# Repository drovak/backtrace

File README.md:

# backtrace
Automated DEC backplane tracing tool

Double-height Flip-Chip card implementing a set of shift registers to scan the card edge 
connectors for continuity.

Driver card for driving a large number of Flip-Chip cards.

This project is still incomplete and untested, but prototype hardware has been ordered.

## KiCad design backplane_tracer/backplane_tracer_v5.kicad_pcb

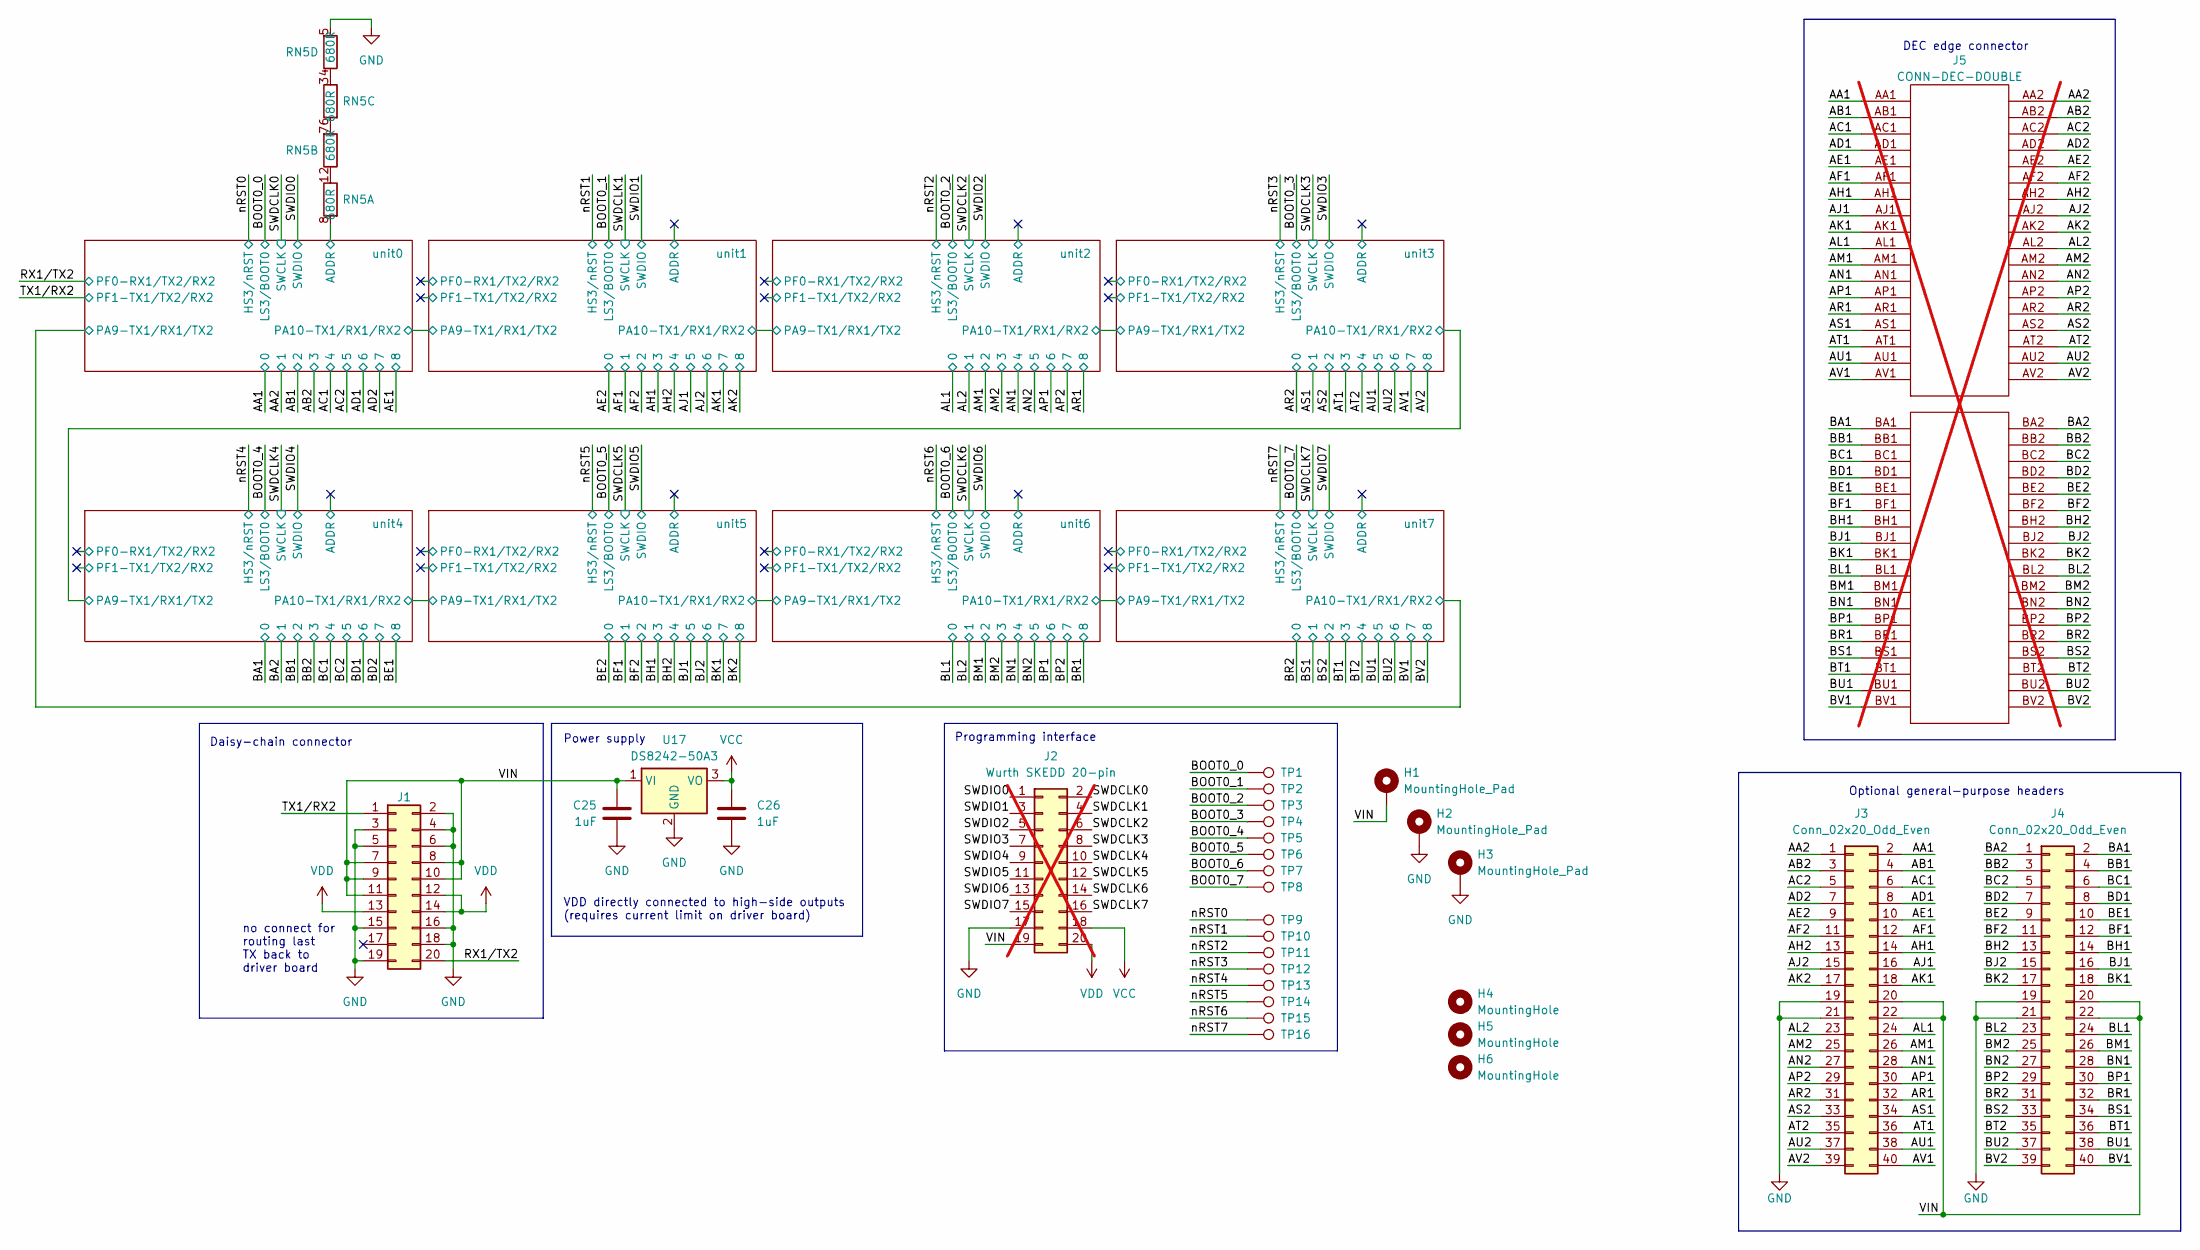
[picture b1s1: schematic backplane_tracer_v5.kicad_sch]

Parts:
C25, C26: 1uF; C_0603_1608Metric; LCSC C15849
H1, H2, H3: MountingHole_Pad; MountingHole_3.7mm_Pad_Via
H4, H5, H6: MountingHole; JLCPCB_Tooling_Hole
J1: 2x10 right angle IDC connector, 2.54mm pitch; IDC-Header_2x10_P2.54mm_Horizontal; LCSC C5372876
J2: Wurth SKEDD 20-pin; wurth_skedd_490107672012; not fitted
J3, J4: Conn_02x20_Odd_Even; PinHeader_2x20_P2.54mm_Vertical; LCSC C5224014
J5: CONN-DEC-DOUBLE; not fitted
RN5: 680R; R_Array_Convex_4x0603; LCSC C12035
TP1, TP2, TP3, TP4, TP5, TP6, TP7, TP8, TP9, TP10, TP11, TP12, TP13, TP14, TP15, TP16: TestPoint; TestPoint_Pad_D1.0mm
U17: DS8242-50A3; SOT-89-3; LCSC C5884136

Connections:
/AA1: J3.2, J5.AA1; also elsewhere on the board
/AA2: J3.1, J5.AA2; also elsewhere on the board
/AB1: J3.4, J5.AB1; also elsewhere on the board
/AB2: J3.3, J5.AB2; also elsewhere on the board
/AC1: J3.6, J5.AC1; also elsewhere on the board
/AC2: J3.5, J5.AC2; also elsewhere on the board
/AD1: J3.8, J5.AD1; also elsewhere on the board
/AD2: J3.7, J5.AD2; also elsewhere on the board
/AE1: J3.10, J5.AE1; also elsewhere on the board
/AE2: J3.9, J5.AE2; also elsewhere on the board
/AF1: J3.12, J5.AF1; also elsewhere on the board
/AF2: J3.11, J5.AF2; also elsewhere on the board
/AH1: J3.14, J5.AH1; also elsewhere on the board
/AH2: J3.13, J5.AH2; also elsewhere on the board
/AJ1: J3.16, J5.AJ1; also elsewhere on the board
/AJ2: J3.15, J5.AJ2; also elsewhere on the board
/AK1: J3.18, J5.AK1; also elsewhere on the board
/AK2: J3.17, J5.AK2; also elsewhere on the board
/AL1: J3.24, J5.AL1; also elsewhere on the board
/AL2: J3.23, J5.AL2; also elsewhere on the board
/AM1: J3.26, J5.AM1; also elsewhere on the board
/AM2: J3.25, J5.AM2; also elsewhere on the board
/AN1: J3.28, J5.AN1; also elsewhere on the board
/AN2: J3.27, J5.AN2; also elsewhere on the board
/AP1: J3.30, J5.AP1; also elsewhere on the board
/AP2: J3.29, J5.AP2; also elsewhere on the board
/AR1: J3.32, J5.AR1; also elsewhere on the board
/AR2: J3.31, J5.AR2; also elsewhere on the board
/AS1: J3.34, J5.AS1; also elsewhere on the board
/AS2: J3.33, J5.AS2; also elsewhere on the board
/AT1: J3.36, J5.AT1; also elsewhere on the board
/AT2: J3.35, J5.AT2; also elsewhere on the board
/AU1: J3.38, J5.AU1; also elsewhere on the board
/AU2: J3.37, J5.AU2; also elsewhere on the board
/AV1: J3.40, J5.AV1; also elsewhere on the board
/AV2: J3.39, J5.AV2; also elsewhere on the board
/BA1: J4.2, J5.BA1; also elsewhere on the board
/BA2: J4.1, J5.BA2; also elsewhere on the board
/BB1: J4.4, J5.BB1; also elsewhere on the board
/BB2: J4.3, J5.BB2; also elsewhere on the board
/BC1: J4.6, J5.BC1; also elsewhere on the board
/BC2: J4.5, J5.BC2; also elsewhere on the board
/BD1: J4.8, J5.BD1; also elsewhere on the board
/BD2: J4.7, J5.BD2; also elsewhere on the board
/BE1: J4.10, J5.BE1; also elsewhere on the board
/BE2: J4.9, J5.BE2; also elsewhere on the board
/BF1: J4.12, J5.BF1; also elsewhere on the board
/BF2: J4.11, J5.BF2; also elsewhere on the board
/BH1: J4.14, J5.BH1; also elsewhere on the board
/BH2: J4.13, J5.BH2; also elsewhere on the board
/BJ1: J4.16, J5.BJ1; also elsewhere on the board
/BJ2: J4.15, J5.BJ2; also elsewhere on the board
/BK1: J4.18, J5.BK1; also elsewhere on the board
/BK2: J4.17, J5.BK2; also elsewhere on the board
/BL1: J4.24, J5.BL1; also elsewhere on the board
/BL2: J4.23, J5.BL2; also elsewhere on the board
/BM1: J4.26, J5.BM1; also elsewhere on the board
/BM2: J4.25, J5.BM2; also elsewhere on the board
/BN1: J4.28, J5.BN1; also elsewhere on the board
/BN2: J4.27, J5.BN2; also elsewhere on the board
/BOOT0_0: TP1.1; also elsewhere on the board
/BOOT0_1: TP2.1; also elsewhere on the board
/BOOT0_2: TP3.1; also elsewhere on the board
/BOOT0_3: TP4.1; also elsewhere on the board
/BOOT0_4: TP5.1; also elsewhere on the board
/BOOT0_5: TP6.1; also elsewhere on the board
/BOOT0_6: TP7.1; also elsewhere on the board
/BOOT0_7: TP8.1; also elsewhere on the board
/BP1: J4.30, J5.BP1; also elsewhere on the board
/BP2: J4.29, J5.BP2; also elsewhere on the board
/BR1: J4.32, J5.BR1; also elsewhere on the board
/BR2: J4.31, J5.BR2; also elsewhere on the board
/BS1: J4.34, J5.BS1; also elsewhere on the board
/BS2: J4.33, J5.BS2; also elsewhere on the board
/BT1: J4.36, J5.BT1; also elsewhere on the board
/BT2: J4.35, J5.BT2; also elsewhere on the board
/BU1: J4.38, J5.BU1; also elsewhere on the board
/BU2: J4.37, J5.BU2; also elsewhere on the board
/BV1: J4.40, J5.BV1; also elsewhere on the board
/BV2: J4.39, J5.BV2; also elsewhere on the board
/RX1/TX2: J1.20; also elsewhere on the board
/SWDCLK0: J2.2; also elsewhere on the board
/SWDCLK1: J2.4; also elsewhere on the board
/SWDCLK2: J2.6; also elsewhere on the board
/SWDCLK3: J2.8; also elsewhere on the board
/SWDCLK4: J2.10; also elsewhere on the board
/SWDCLK5: J2.12; also elsewhere on the board
/SWDCLK6: J2.14; also elsewhere on the board
/SWDCLK7: J2.16; also elsewhere on the board
/SWDIO0: J2.1; also elsewhere on the board
/SWDIO1: J2.3; also elsewhere on the board
/SWDIO2: J2.5; also elsewhere on the board
/SWDIO3: J2.7; also elsewhere on the board
/SWDIO4: J2.9; also elsewhere on the board
/SWDIO5: J2.11; also elsewhere on the board
/SWDIO6: J2.13; also elsewhere on the board
/SWDIO7: J2.15; also elsewhere on the board
/TX1/RX2: J1.1; also elsewhere on the board
/VIN: C25.1, H1.1, J1.7, J1.8, J1.9, J1.10, J1.11, J2.19, J3.20, J3.22, J4.20, J4.22, U17.1 (VI)
/nRST0: TP9.1; also elsewhere on the board
/nRST1: TP10.1; also elsewhere on the board
/nRST2: TP11.1; also elsewhere on the board
/nRST3: TP12.1; also elsewhere on the board
/nRST4: TP13.1; also elsewhere on the board
/nRST5: TP14.1; also elsewhere on the board
/nRST6: TP15.1; also elsewhere on the board
/nRST7: TP16.1; also elsewhere on the board
/unit0/ADDR: RN5.8 (R1.2); also elsewhere on the board
GND: C25.2, C26.2, H2.1, H3.1, J1.2, J1.3, J1.4, J1.5, J1.6, J1.15, J1.16, J1.18, J1.19, J2.17, J3.19, J3.21, J4.19, J4.21, RN5.5 (R4.2), U17.2 (GND); also elsewhere on the board
unnamed: RN5.1 (R1.1), RN5.2 (R2.1)
unnamed: RN5.6 (R3.2), RN5.7 (R2.2)
unnamed: RN5.3 (R3.1), RN5.4 (R4.1)
VCC: C26.1, J2.18, U17.3 (VO); also elsewhere on the board
VDD: J1.12, J1.13, J1.14, J2.20; also elsewhere on the board

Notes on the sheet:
Daisy-chain connector
Power supply
Optional general-purpose headers
no connect for routing last TX back to driver board
VDD directly connected to high-side outputs (requires current limit on driver board)
DEC edge connector
Programming interface

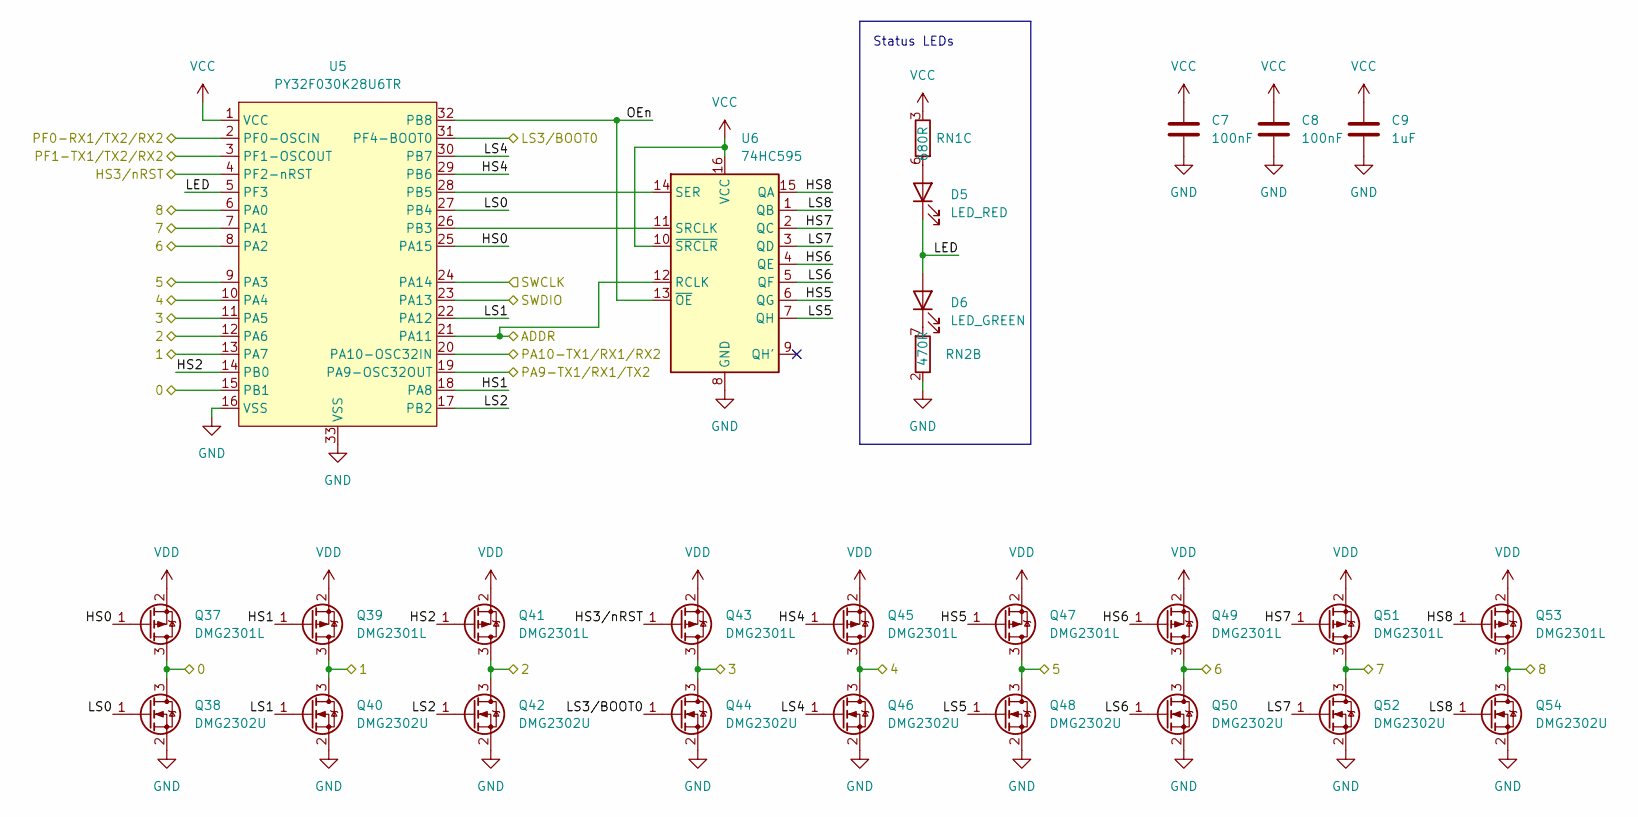
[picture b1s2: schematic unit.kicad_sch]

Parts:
C7, C8: 100nF; C_0603_1608Metric; LCSC C14663
C9: 1uF; C_0603_1608Metric; LCSC C15849
D5: LED_RED; LED_0603_1608Metric; LCSC C7496820
D6: LED_GREEN; LED_0603_1608Metric; LCSC C7496818
Q37, Q39, Q41, Q43, Q45, Q47, Q49, Q51, Q53: DMG2301L; SOT-23_alt_silk; LCSC C7499856
Q38, Q40, Q42, Q44, Q46, Q48, Q50, Q52, Q54: DMG2302U; SOT-23_alt_silk; LCSC C7431443
RN1: 680R; R_Array_Convex_4x0603; LCSC C12035
RN2: 470R; R_Array_Convex_4x0603; LCSC C25510
U5: PY32F030K28U6TR; QFN-32-1EP_5x5mm_P0.5mm_EP3.6x3.6mm; LCSC C3018718
U6: 74HC595; SOP-16_3.9x9.9mm_P1.27mm; LCSC C18164493

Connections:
/AL1: Q37.3 (D), Q38.3 (D), U5.15 (PB1); also elsewhere on the board
/AL2: Q39.3 (D), Q40.3 (D), U5.13 (PA7); also elsewhere on the board
/AM1: Q41.3 (D), Q42.3 (D), U5.12 (PA6); also elsewhere on the board
/AM2: Q43.3 (D), Q44.3 (D), U5.11 (PA5); also elsewhere on the board
/AN1: Q45.3 (D), Q46.3 (D), U5.10 (PA4); also elsewhere on the board
/AN2: Q47.3 (D), Q48.3 (D), U5.9 (PA3); also elsewhere on the board
/AP1: Q49.3 (D), Q50.3 (D), U5.8 (PA2); also elsewhere on the board
/AP2: Q51.3 (D), Q52.3 (D), U5.7 (PA1); also elsewhere on the board
/AR1: Q53.3 (D), Q54.3 (D), U5.6 (PA0); also elsewhere on the board
/BOOT0_2: Q44.1 (G), U5.31 (PF4-BOOT0); also elsewhere on the board
/SWDCLK2: U5.24 (PA14); also elsewhere on the board
/SWDIO2: U5.23 (PA13); also elsewhere on the board
/nRST2: Q43.1 (G), U5.4 (PF2-nRST); also elsewhere on the board
/unit1/PA10-TX1/RX1/RX2: U5.19 (PA9-OSC32OUT); also elsewhere on the board
/unit2/ADDR: U5.21 (PA11), U6.12 (RCLK)
/unit2/HS0: Q37.1 (G), U5.25 (PA15)
/unit2/HS1: Q39.1 (G), U5.18 (PA8)
/unit2/HS2: Q41.1 (G), U5.14 (PB0)
/unit2/HS4: Q45.1 (G), U5.29 (PB6)
/unit2/HS5: Q47.1 (G), U6.6 (QG)
/unit2/HS6: Q49.1 (G), U6.4 (QE)
/unit2/HS7: Q51.1 (G), U6.2 (QC)
/unit2/HS8: Q53.1 (G), U6.15 (QA)
/unit2/LED: D5.1 (K), D6.2 (A), U5.5 (PF3)
/unit2/LS0: Q38.1 (G), U5.27 (PB4)
/unit2/LS1: Q40.1 (G), U5.22 (PA12)
/unit2/LS2: Q42.1 (G), U5.17 (PB2)
/unit2/LS4: Q46.1 (G), U5.30 (PB7)
/unit2/LS5: Q48.1 (G), U6.7 (QH)
/unit2/LS6: Q50.1 (G), U6.5 (QF)
/unit2/LS7: Q52.1 (G), U6.3 (QD)
/unit2/LS8: Q54.1 (G), U6.1 (QB)
/unit2/OEn: U5.32 (PB8), U6.13 (~OE)
/unit2/PA10-TX1/RX1/RX2: U5.20 (PA10-OSC32IN); also elsewhere on the board
/unit2/PF0-RX1/TX2/RX2: U5.2 (PF0-OSCIN)
/unit2/PF1-TX1/TX2/RX2: U5.3 (PF1-OSCOUT)
GND: C7.2, C8.2, C9.2, Q38.2 (S), Q40.2 (S), Q42.2 (S), Q44.2 (S), Q46.2 (S), Q48.2 (S), Q50.2 (S), Q52.2 (S), Q54.2 (S), RN2.1 (R1.1), RN2.2 (R2.1), RN2.3 (R3.1), RN2.4 (R4.1), U5.16 (VSS), U5.33 (VSS), U6.8 (GND); also elsewhere on the board
unnamed 282: RN1.8 (R1.2); also elsewhere on the board
unnamed 283: RN2.5 (R4.2); also elsewhere on the board
unnamed 284: RN1.7 (R2.2); also elsewhere on the board
unnamed 285: RN2.6 (R3.2); also elsewhere on the board
unnamed: D5.2 (A), RN1.6 (R3.2)
unnamed: D6.1 (K), RN2.7 (R2.2)
unnamed 288: RN1.5 (R4.2); also elsewhere on the board
unnamed 289: RN2.8 (R1.2); also elsewhere on the board
unnamed: U5.26 (PB3), U6.11 (SRCLK)
unnamed: U5.28 (PB5), U6.14 (SER)
VCC: C7.1, C8.1, C9.1, RN1.1 (R1.1), RN1.2 (R2.1), RN1.3 (R3.1), RN1.4 (R4.1), U5.1 (VCC), U6.10 (~SRCLR), U6.16 (VCC); also elsewhere on the board
VDD: Q37.2 (S), Q39.2 (S), Q41.2 (S), Q43.2 (S), Q45.2 (S), Q47.2 (S), Q49.2 (S), Q51.2 (S), Q53.2 (S); also elsewhere on the board

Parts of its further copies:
C1, C2, C4, C5, C10, C11, C13, C14, C16, C17, C19, C20, C22, C23: 100nF; C_0603_1608Metric; LCSC C14663
C3, C6, C12, C15, C18, C21, C24: 1uF; C_0603_1608Metric; LCSC C15849
D1, D3, D7, D9, D11, D13, D15: LED_RED; LED_0603_1608Metric; LCSC C7496820
D2, D4, D8, D10, D12, D14, D16: LED_GREEN; LED_0603_1608Metric; LCSC C7496818
Q1, Q3, Q5, Q7, Q9, Q11, Q13, Q15, Q17, Q19, Q21, Q23, Q25, Q27, Q29, Q31, Q33, Q35, Q55, Q57, Q59, Q61, Q63, Q65, Q67, Q69, Q71, Q73, Q75, Q77, Q79, Q81, Q83, Q85, Q87, Q89, Q91, Q93, Q95, Q97, Q99, Q101, Q103, Q105, Q107, Q109, Q111, Q113, Q115, Q117, Q119, Q121, Q123, Q125, Q127, Q129, Q131, Q133, Q135, Q137, Q139, Q141, Q143: DMG2301L; SOT-23_alt_silk; LCSC C7499856
Q2, Q4, Q6, Q8, Q10, Q12, Q14, Q16, Q18, Q20, Q22, Q24, Q26, Q28, Q30, Q32, Q34, Q36, Q56, Q58, Q60, Q62, Q64, Q66, Q68, Q70, Q72, Q74, Q76, Q78, Q80, Q82, Q84, Q86, Q88, Q90, Q92, Q94, Q96, Q98, Q100, Q102, Q104, Q106, Q108, Q110, Q112, Q114, Q116, Q118, Q120, Q122, Q124, Q126, Q128, Q130, Q132, Q134, Q136, Q138, Q140, Q142, Q144: DMG2302U; SOT-23_alt_silk; LCSC C7431443
RN3: 680R; R_Array_Convex_4x0603; LCSC C12035
RN4: 470R; R_Array_Convex_4x0603; LCSC C25510
U1, U3, U7, U9, U11, U13, U15: PY32F030K28U6TR; QFN-32-1EP_5x5mm_P0.5mm_EP3.6x3.6mm; LCSC C3018718
U2, U4, U8, U10, U12, U14, U16: 74HC595; SOP-16_3.9x9.9mm_P1.27mm; LCSC C18164493

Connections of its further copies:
/AA1: Q1.3 (D), Q2.3 (D), U1.15 (PB1); also elsewhere on the board
/AA2: Q3.3 (D), Q4.3 (D), U1.13 (PA7); also elsewhere on the board
/AB1: Q5.3 (D), Q6.3 (D), U1.12 (PA6); also elsewhere on the board
/AB2: Q7.3 (D), Q8.3 (D), U1.11 (PA5); also elsewhere on the board
/AC1: Q9.3 (D), Q10.3 (D), U1.10 (PA4); also elsewhere on the board
/AC2: Q11.3 (D), Q12.3 (D), U1.9 (PA3); also elsewhere on the board
/AD1: Q13.3 (D), Q14.3 (D), U1.8 (PA2); also elsewhere on the board
/AD2: Q15.3 (D), Q16.3 (D), U1.7 (PA1); also elsewhere on the board
/AE1: Q17.3 (D), Q18.3 (D), U1.6 (PA0); also elsewhere on the board
/AE2: Q19.3 (D), Q20.3 (D), U3.15 (PB1); also elsewhere on the board
/AF1: Q21.3 (D), Q22.3 (D), U3.13 (PA7); also elsewhere on the board
/AF2: Q23.3 (D), Q24.3 (D), U3.12 (PA6); also elsewhere on the board
/AH1: Q25.3 (D), Q26.3 (D), U3.11 (PA5); also elsewhere on the board
/AH2: Q27.3 (D), Q28.3 (D), U3.10 (PA4); also elsewhere on the board
/AJ1: Q29.3 (D), Q30.3 (D), U3.9 (PA3); also elsewhere on the board
/AJ2: Q31.3 (D), Q32.3 (D), U3.8 (PA2); also elsewhere on the board
/AK1: Q33.3 (D), Q34.3 (D), U3.7 (PA1); also elsewhere on the board
/AK2: Q35.3 (D), Q36.3 (D), U3.6 (PA0); also elsewhere on the board
/AR2: Q55.3 (D), Q56.3 (D), U7.15 (PB1); also elsewhere on the board
/AS1: Q57.3 (D), Q58.3 (D), U7.13 (PA7); also elsewhere on the board
/AS2: Q59.3 (D), Q60.3 (D), U7.12 (PA6); also elsewhere on the board
/AT1: Q61.3 (D), Q62.3 (D), U7.11 (PA5); also elsewhere on the board
/AT2: Q63.3 (D), Q64.3 (D), U7.10 (PA4); also elsewhere on the board
/AU1: Q65.3 (D), Q66.3 (D), U7.9 (PA3); also elsewhere on the board
/AU2: Q67.3 (D), Q68.3 (D), U7.8 (PA2); also elsewhere on the board
/AV1: Q69.3 (D), Q70.3 (D), U7.7 (PA1); also elsewhere on the board
/AV2: Q71.3 (D), Q72.3 (D), U7.6 (PA0); also elsewhere on the board
/BA1: Q73.3 (D), Q74.3 (D), U9.15 (PB1); also elsewhere on the board
/BA2: Q75.3 (D), Q76.3 (D), U9.13 (PA7); also elsewhere on the board
/BB1: Q77.3 (D), Q78.3 (D), U9.12 (PA6); also elsewhere on the board
/BB2: Q79.3 (D), Q80.3 (D), U9.11 (PA5); also elsewhere on the board
/BC1: Q81.3 (D), Q82.3 (D), U9.10 (PA4); also elsewhere on the board
/BC2: Q83.3 (D), Q84.3 (D), U9.9 (PA3); also elsewhere on the board
/BD1: Q85.3 (D), Q86.3 (D), U9.8 (PA2); also elsewhere on the board
/BD2: Q87.3 (D), Q88.3 (D), U9.7 (PA1); also elsewhere on the board
/BE1: Q89.3 (D), Q90.3 (D), U9.6 (PA0); also elsewhere on the board
/BE2: Q91.3 (D), Q92.3 (D), U11.15 (PB1); also elsewhere on the board
/BF1: Q93.3 (D), Q94.3 (D), U11.13 (PA7); also elsewhere on the board
/BF2: Q95.3 (D), Q96.3 (D), U11.12 (PA6); also elsewhere on the board
/BH1: Q97.3 (D), Q98.3 (D), U11.11 (PA5); also elsewhere on the board
/BH2: Q99.3 (D), Q100.3 (D), U11.10 (PA4); also elsewhere on the board
/BJ1: Q101.3 (D), Q102.3 (D), U11.9 (PA3); also elsewhere on the board
/BJ2: Q103.3 (D), Q104.3 (D), U11.8 (PA2); also elsewhere on the board
/BK1: Q105.3 (D), Q106.3 (D), U11.7 (PA1); also elsewhere on the board
/BK2: Q107.3 (D), Q108.3 (D), U11.6 (PA0); also elsewhere on the board
/BL1: Q109.3 (D), Q110.3 (D), U13.15 (PB1); also elsewhere on the board
/BL2: Q111.3 (D), Q112.3 (D), U13.13 (PA7); also elsewhere on the board
/BM1: Q113.3 (D), Q114.3 (D), U13.12 (PA6); also elsewhere on the board
/BM2: Q115.3 (D), Q116.3 (D), U13.11 (PA5); also elsewhere on the board
/BN1: Q117.3 (D), Q118.3 (D), U13.10 (PA4); also elsewhere on the board
/BN2: Q119.3 (D), Q120.3 (D), U13.9 (PA3); also elsewhere on the board
/BOOT0_0: Q8.1 (G), U1.31 (PF4-BOOT0); also elsewhere on the board
/BOOT0_1: Q26.1 (G), U3.31 (PF4-BOOT0); also elsewhere on the board
/BOOT0_3: Q62.1 (G), U7.31 (PF4-BOOT0); also elsewhere on the board
/BOOT0_4: Q80.1 (G), U9.31 (PF4-BOOT0); also elsewhere on the board
/BOOT0_5: Q98.1 (G), U11.31 (PF4-BOOT0); also elsewhere on the board
/BOOT0_6: Q116.1 (G), U13.31 (PF4-BOOT0); also elsewhere on the board
/BOOT0_7: Q134.1 (G), U15.31 (PF4-BOOT0); also elsewhere on the board
/BP1: Q121.3 (D), Q122.3 (D), U13.8 (PA2); also elsewhere on the board
/BP2: Q123.3 (D), Q124.3 (D), U13.7 (PA1); also elsewhere on the board
/BR1: Q125.3 (D), Q126.3 (D), U13.6 (PA0); also elsewhere on the board
/BR2: Q127.3 (D), Q128.3 (D), U15.15 (PB1); also elsewhere on the board
/BS1: Q129.3 (D), Q130.3 (D), U15.13 (PA7); also elsewhere on the board
/BS2: Q131.3 (D), Q132.3 (D), U15.12 (PA6); also elsewhere on the board
/BT1: Q133.3 (D), Q134.3 (D), U15.11 (PA5); also elsewhere on the board
/BT2: Q135.3 (D), Q136.3 (D), U15.10 (PA4); also elsewhere on the board
/BU1: Q137.3 (D), Q138.3 (D), U15.9 (PA3); also elsewhere on the board
/BU2: Q139.3 (D), Q140.3 (D), U15.8 (PA2); also elsewhere on the board
/BV1: Q141.3 (D), Q142.3 (D), U15.7 (PA1); also elsewhere on the board
/BV2: Q143.3 (D), Q144.3 (D), U15.6 (PA0); also elsewhere on the board
/RX1/TX2: U1.2 (PF0-OSCIN); also elsewhere on the board
/SWDCLK0: U1.24 (PA14); also elsewhere on the board
/SWDCLK1: U3.24 (PA14); also elsewhere on the board
/SWDCLK3: U7.24 (PA14); also elsewhere on the board
/SWDCLK4: U9.24 (PA14); also elsewhere on the board
/SWDCLK5: U11.24 (PA14); also elsewhere on the board
/SWDCLK6: U13.24 (PA14); also elsewhere on the board
/SWDCLK7: U15.24 (PA14); also elsewhere on the board
/SWDIO0: U1.23 (PA13); also elsewhere on the board
/SWDIO1: U3.23 (PA13); also elsewhere on the board
/SWDIO3: U7.23 (PA13); also elsewhere on the board
/SWDIO4: U9.23 (PA13); also elsewhere on the board
/SWDIO5: U11.23 (PA13); also elsewhere on the board
/SWDIO6: U13.23 (PA13); also elsewhere on the board
/SWDIO7: U15.23 (PA13); also elsewhere on the board
/TX1/RX2: U1.3 (PF1-OSCOUT); also elsewhere on the board
/nRST0: Q7.1 (G), U1.4 (PF2-nRST); also elsewhere on the board
/nRST1: Q25.1 (G), U3.4 (PF2-nRST); also elsewhere on the board
/nRST3: Q61.1 (G), U7.4 (PF2-nRST); also elsewhere on the board
/nRST4: Q79.1 (G), U9.4 (PF2-nRST); also elsewhere on the board
/nRST5: Q97.1 (G), U11.4 (PF2-nRST); also elsewhere on the board
/nRST6: Q115.1 (G), U13.4 (PF2-nRST); also elsewhere on the board
/nRST7: Q133.1 (G), U15.4 (PF2-nRST); also elsewhere on the board
/unit0/ADDR: U1.21 (PA11), U2.12 (RCLK); also elsewhere on the board
/unit0/HS0: Q1.1 (G), U1.25 (PA15)
/unit0/HS1: Q3.1 (G), U1.18 (PA8)
/unit0/HS2: Q5.1 (G), U1.14 (PB0)
/unit0/HS4: Q9.1 (G), U1.29 (PB6)
/unit0/HS5: Q11.1 (G), U2.6 (QG)
/unit0/HS6: Q13.1 (G), U2.4 (QE)
/unit0/HS7: Q15.1 (G), U2.2 (QC)
/unit0/HS8: Q17.1 (G), U2.15 (QA)
/unit0/LED: D1.1 (K), D2.2 (A), U1.5 (PF3)
/unit0/LS0: Q2.1 (G), U1.27 (PB4)
/unit0/LS1: Q4.1 (G), U1.22 (PA12)
/unit0/LS2: Q6.1 (G), U1.17 (PB2)
/unit0/LS4: Q10.1 (G), U1.30 (PB7)
/unit0/LS5: Q12.1 (G), U2.7 (QH)
/unit0/LS6: Q14.1 (G), U2.5 (QF)
/unit0/LS7: Q16.1 (G), U2.3 (QD)
/unit0/LS8: Q18.1 (G), U2.1 (QB)
/unit0/OEn: U1.32 (PB8), U2.13 (~OE)
/unit0/PA9-TX1/RX1/TX2: U1.19 (PA9-OSC32OUT), U15.20 (PA10-OSC32IN)
/unit0/PA10-TX1/RX1/RX2: U1.20 (PA10-OSC32IN), U3.19 (PA9-OSC32OUT)
/unit1/ADDR: U3.21 (PA11), U4.12 (RCLK)
/unit1/HS0: Q19.1 (G), U3.25 (PA15)
/unit1/HS1: Q21.1 (G), U3.18 (PA8)
/unit1/HS2: Q23.1 (G), U3.14 (PB0)
/unit1/HS4: Q27.1 (G), U3.29 (PB6)
/unit1/HS5: Q29.1 (G), U4.6 (QG)
/unit1/HS6: Q31.1 (G), U4.4 (QE)
/unit1/HS7: Q33.1 (G), U4.2 (QC)
/unit1/HS8: Q35.1 (G), U4.15 (QA)
/unit1/LED: D3.1 (K), D4.2 (A), U3.5 (PF3)
/unit1/LS0: Q20.1 (G), U3.27 (PB4)
/unit1/LS1: Q22.1 (G), U3.22 (PA12)
/unit1/LS2: Q24.1 (G), U3.17 (PB2)
/unit1/LS4: Q28.1 (G), U3.30 (PB7)
/unit1/LS5: Q30.1 (G), U4.7 (QH)
/unit1/LS6: Q32.1 (G), U4.5 (QF)
/unit1/LS7: Q34.1 (G), U4.3 (QD)
/unit1/LS8: Q36.1 (G), U4.1 (QB)
/unit1/OEn: U3.32 (PB8), U4.13 (~OE)
/unit1/PA10-TX1/RX1/RX2: U3.20 (PA10-OSC32IN); also elsewhere on the board
/unit1/PF0-RX1/TX2/RX2: U3.2 (PF0-OSCIN)
/unit1/PF1-TX1/TX2/RX2: U3.3 (PF1-OSCOUT)
/unit2/PA10-TX1/RX1/RX2: U7.19 (PA9-OSC32OUT); also elsewhere on the board
/unit3/ADDR: U7.21 (PA11), U8.12 (RCLK)
/unit3/HS0: Q55.1 (G), U7.25 (PA15)
/unit3/HS1: Q57.1 (G), U7.18 (PA8)
/unit3/HS2: Q59.1 (G), U7.14 (PB0)
/unit3/HS4: Q63.1 (G), U7.29 (PB6)
/unit3/HS5: Q65.1 (G), U8.6 (QG)
/unit3/HS6: Q67.1 (G), U8.4 (QE)
/unit3/HS7: Q69.1 (G), U8.2 (QC)
/unit3/HS8: Q71.1 (G), U8.15 (QA)
/unit3/LED: D7.1 (K), D8.2 (A), U7.5 (PF3)
/unit3/LS0: Q56.1 (G), U7.27 (PB4)
/unit3/LS1: Q58.1 (G), U7.22 (PA12)
/unit3/LS2: Q60.1 (G), U7.17 (PB2)
/unit3/LS4: Q64.1 (G), U7.30 (PB7)
/unit3/LS5: Q66.1 (G), U8.7 (QH)
/unit3/LS6: Q68.1 (G), U8.5 (QF)
/unit3/LS7: Q70.1 (G), U8.3 (QD)
/unit3/LS8: Q72.1 (G), U8.1 (QB)
/unit3/OEn: U7.32 (PB8), U8.13 (~OE)
/unit3/PA10-TX1/RX1/RX2: U7.20 (PA10-OSC32IN), U9.19 (PA9-OSC32OUT)
/unit3/PF0-RX1/TX2/RX2: U7.2 (PF0-OSCIN)
/unit3/PF1-TX1/TX2/RX2: U7.3 (PF1-OSCOUT)
/unit4/ADDR: U9.21 (PA11), U10.12 (RCLK)
/unit4/HS0: Q73.1 (G), U9.25 (PA15)
/unit4/HS1: Q75.1 (G), U9.18 (PA8)
/unit4/HS2: Q77.1 (G), U9.14 (PB0)
/unit4/HS4: Q81.1 (G), U9.29 (PB6)
/unit4/HS5: Q83.1 (G), U10.6 (QG)
/unit4/HS6: Q85.1 (G), U10.4 (QE)
/unit4/HS7: Q87.1 (G), U10.2 (QC)
/unit4/HS8: Q89.1 (G), U10.15 (QA)
/unit4/LED: D9.1 (K), D10.2 (A), U9.5 (PF3)
/unit4/LS0: Q74.1 (G), U9.27 (PB4)
/unit4/LS1: Q76.1 (G), U9.22 (PA12)
/unit4/LS2: Q78.1 (G), U9.17 (PB2)
/unit4/LS4: Q82.1 (G), U9.30 (PB7)
/unit4/LS5: Q84.1 (G), U10.7 (QH)
/unit4/LS6: Q86.1 (G), U10.5 (QF)
/unit4/LS7: Q88.1 (G), U10.3 (QD)
/unit4/LS8: Q90.1 (G), U10.1 (QB)
/unit4/OEn: U9.32 (PB8), U10.13 (~OE)
/unit4/PA10-TX1/RX1/RX2: U9.20 (PA10-OSC32IN), U11.19 (PA9-OSC32OUT)
/unit4/PF0-RX1/TX2/RX2: U9.2 (PF0-OSCIN)
/unit4/PF1-TX1/TX2/RX2: U9.3 (PF1-OSCOUT)
/unit5/ADDR: U11.21 (PA11), U12.12 (RCLK)
/unit5/HS0: Q91.1 (G), U11.25 (PA15)
/unit5/HS1: Q93.1 (G), U11.18 (PA8)
/unit5/HS2: Q95.1 (G), U11.14 (PB0)
/unit5/HS4: Q99.1 (G), U11.29 (PB6)
/unit5/HS5: Q101.1 (G), U12.6 (QG)
/unit5/HS6: Q103.1 (G), U12.4 (QE)
/unit5/HS7: Q105.1 (G), U12.2 (QC)
/unit5/HS8: Q107.1 (G), U12.15 (QA)
/unit5/LED: D11.1 (K), D12.2 (A), U11.5 (PF3)
/unit5/LS0: Q92.1 (G), U11.27 (PB4)
/unit5/LS1: Q94.1 (G), U11.22 (PA12)
/unit5/LS2: Q96.1 (G), U11.17 (PB2)
/unit5/LS4: Q100.1 (G), U11.30 (PB7)
/unit5/LS5: Q102.1 (G), U12.7 (QH)
/unit5/LS6: Q104.1 (G), U12.5 (QF)
/unit5/LS7: Q106.1 (G), U12.3 (QD)
/unit5/LS8: Q108.1 (G), U12.1 (QB)
/unit5/OEn: U11.32 (PB8), U12.13 (~OE)
/unit5/PA10-TX1/RX1/RX2: U11.20 (PA10-OSC32IN), U13.19 (PA9-OSC32OUT)
/unit5/PF0-RX1/TX2/RX2: U11.2 (PF0-OSCIN)
/unit5/PF1-TX1/TX2/RX2: U11.3 (PF1-OSCOUT)
/unit6/ADDR: U13.21 (PA11), U14.12 (RCLK)
/unit6/HS0: Q109.1 (G), U13.25 (PA15)
/unit6/HS1: Q111.1 (G), U13.18 (PA8)
/unit6/HS2: Q113.1 (G), U13.14 (PB0)
/unit6/HS4: Q117.1 (G), U13.29 (PB6)
/unit6/HS5: Q119.1 (G), U14.6 (QG)
/unit6/HS6: Q121.1 (G), U14.4 (QE)
/unit6/HS7: Q123.1 (G), U14.2 (QC)
/unit6/HS8: Q125.1 (G), U14.15 (QA)
/unit6/LED: D13.1 (K), D14.2 (A), U13.5 (PF3)
/unit6/LS0: Q110.1 (G), U13.27 (PB4)
/unit6/LS1: Q112.1 (G), U13.22 (PA12)
/unit6/LS2: Q114.1 (G), U13.17 (PB2)
/unit6/LS4: Q118.1 (G), U13.30 (PB7)
/unit6/LS5: Q120.1 (G), U14.7 (QH)
/unit6/LS6: Q122.1 (G), U14.5 (QF)
/unit6/LS7: Q124.1 (G), U14.3 (QD)
/unit6/LS8: Q126.1 (G), U14.1 (QB)
/unit6/OEn: U13.32 (PB8), U14.13 (~OE)
/unit6/PA10-TX1/RX1/RX2: U13.20 (PA10-OSC32IN), U15.19 (PA9-OSC32OUT)
/unit6/PF0-RX1/TX2/RX2: U13.2 (PF0-OSCIN)
/unit6/PF1-TX1/TX2/RX2: U13.3 (PF1-OSCOUT)
/unit7/ADDR: U15.21 (PA11), U16.12 (RCLK)
/unit7/HS0: Q127.1 (G), U15.25 (PA15)
/unit7/HS1: Q129.1 (G), U15.18 (PA8)
/unit7/HS2: Q131.1 (G), U15.14 (PB0)
/unit7/HS4: Q135.1 (G), U15.29 (PB6)
/unit7/HS5: Q137.1 (G), U16.6 (QG)
/unit7/HS6: Q139.1 (G), U16.4 (QE)
/unit7/HS7: Q141.1 (G), U16.2 (QC)
/unit7/HS8: Q143.1 (G), U16.15 (QA)
/unit7/LED: D15.1 (K), D16.2 (A), U15.5 (PF3)
/unit7/LS0: Q128.1 (G), U15.27 (PB4)
/unit7/LS1: Q130.1 (G), U15.22 (PA12)
/unit7/LS2: Q132.1 (G), U15.17 (PB2)
/unit7/LS4: Q136.1 (G), U15.30 (PB7)
/unit7/LS5: Q138.1 (G), U16.7 (QH)
/unit7/LS6: Q140.1 (G), U16.5 (QF)
/unit7/LS7: Q142.1 (G), U16.3 (QD)
/unit7/LS8: Q144.1 (G), U16.1 (QB)
/unit7/OEn: U15.32 (PB8), U16.13 (~OE)
/unit7/PF0-RX1/TX2/RX2: U15.2 (PF0-OSCIN)
/unit7/PF1-TX1/TX2/RX2: U15.3 (PF1-OSCOUT)
GND: C1.2, C2.2, C3.2, C4.2, C5.2, C6.2, C10.2, C11.2, C12.2, C13.2, C14.2, C15.2, C16.2, C17.2, C18.2, C19.2, C20.2, C21.2, C22.2, C23.2, C24.2, Q2.2 (S), Q4.2 (S), Q6.2 (S), Q8.2 (S), Q10.2 (S), Q12.2 (S), Q14.2 (S), Q16.2 (S), Q18.2 (S), Q20.2 (S), Q22.2 (S), Q24.2 (S), Q26.2 (S), Q28.2 (S), Q30.2 (S), Q32.2 (S), Q34.2 (S), Q36.2 (S), Q56.2 (S), Q58.2 (S), Q60.2 (S), Q62.2 (S), Q64.2 (S), Q66.2 (S), Q68.2 (S), Q70.2 (S), Q72.2 (S), Q74.2 (S), Q76.2 (S), Q78.2 (S), Q80.2 (S), Q82.2 (S), Q84.2 (S), Q86.2 (S), Q88.2 (S), Q90.2 (S), Q92.2 (S), Q94.2 (S), Q96.2 (S), Q98.2 (S), Q100.2 (S), Q102.2 (S), Q104.2 (S), Q106.2 (S), Q108.2 (S), Q110.2 (S), Q112.2 (S), Q114.2 (S), Q116.2 (S), Q118.2 (S), Q120.2 (S), Q122.2 (S), Q124.2 (S), Q126.2 (S), Q128.2 (S), Q130.2 (S), Q132.2 (S), Q134.2 (S), Q136.2 (S), Q138.2 (S), Q140.2 (S), Q142.2 (S), Q144.2 (S), RN4.1 (R1.1), RN4.2 (R2.1), RN4.3 (R3.1), RN4.4 (R4.1), U1.16 (VSS), U1.33 (VSS), U2.8 (GND), U3.16 (VSS), U3.33 (VSS), U4.8 (GND), U7.16 (VSS), U7.33 (VSS), U8.8 (GND), U9.16 (VSS), U9.33 (VSS), U10.8 (GND), U11.16 (VSS), U11.33 (VSS), U12.8 (GND), U13.16 (VSS), U13.33 (VSS), U14.8 (GND), U15.16 (VSS), U15.33 (VSS), U16.8 (GND); also elsewhere on the board
unnamed 282: D1.2 (A); also elsewhere on the board
unnamed 283: D2.1 (K); also elsewhere on the board
unnamed 284: D3.2 (A); also elsewhere on the board
unnamed 285: D4.1 (K); also elsewhere on the board
unnamed 288: D7.2 (A); also elsewhere on the board
unnamed 289: D8.1 (K); also elsewhere on the board
unnamed: D9.2 (A), RN3.8 (R1.2)
unnamed: D10.1 (K), RN4.5 (R4.2)
unnamed: D11.2 (A), RN3.7 (R2.2)
unnamed: D12.1 (K), RN4.6 (R3.2)
unnamed: D13.2 (A), RN3.6 (R3.2)
unnamed: D14.1 (K), RN4.7 (R2.2)
unnamed: D15.2 (A), RN3.5 (R4.2)
unnamed: D16.1 (K), RN4.8 (R1.2)
unnamed: U1.26 (PB3), U2.11 (SRCLK)
unnamed: U1.28 (PB5), U2.14 (SER)
unnamed: U3.26 (PB3), U4.11 (SRCLK)
unnamed: U3.28 (PB5), U4.14 (SER)
unnamed: U7.26 (PB3), U8.11 (SRCLK)
unnamed: U7.28 (PB5), U8.14 (SER)
unnamed: U9.28 (PB5), U10.14 (SER)
unnamed: U9.26 (PB3), U10.11 (SRCLK)
unnamed: U11.26 (PB3), U12.11 (SRCLK)
unnamed: U11.28 (PB5), U12.14 (SER)
unnamed: U13.26 (PB3), U14.11 (SRCLK)
unnamed: U13.28 (PB5), U14.14 (SER)
unnamed: U15.26 (PB3), U16.11 (SRCLK)
unnamed: U15.28 (PB5), U16.14 (SER)
VCC: C1.1, C2.1, C3.1, C4.1, C5.1, C6.1, C10.1, C11.1, C12.1, C13.1, C14.1, C15.1, C16.1, C17.1, C18.1, C19.1, C20.1, C21.1, C22.1, C23.1, C24.1, RN3.1 (R1.1), RN3.2 (R2.1), RN3.3 (R3.1), RN3.4 (R4.1), U1.1 (VCC), U2.10 (~SRCLR), U2.16 (VCC), U3.1 (VCC), U4.10 (~SRCLR), U4.16 (VCC), U7.1 (VCC), U8.10 (~SRCLR), U8.16 (VCC), U9.1 (VCC), U10.10 (~SRCLR), U10.16 (VCC), U11.1 (VCC), U12.10 (~SRCLR), U12.16 (VCC), U13.1 (VCC), U14.10 (~SRCLR), U14.16 (VCC), U15.1 (VCC), U16.10 (~SRCLR), U16.16 (VCC); also elsewhere on the board
VDD: Q1.2 (S), Q3.2 (S), Q5.2 (S), Q7.2 (S), Q9.2 (S), Q11.2 (S), Q13.2 (S), Q15.2 (S), Q17.2 (S), Q19.2 (S), Q21.2 (S), Q23.2 (S), Q25.2 (S), Q27.2 (S), Q29.2 (S), Q31.2 (S), Q33.2 (S), Q35.2 (S), Q55.2 (S), Q57.2 (S), Q59.2 (S), Q61.2 (S), Q63.2 (S), Q65.2 (S), Q67.2 (S), Q69.2 (S), Q71.2 (S), Q73.2 (S), Q75.2 (S), Q77.2 (S), Q79.2 (S), Q81.2 (S), Q83.2 (S), Q85.2 (S), Q87.2 (S), Q89.2 (S), Q91.2 (S), Q93.2 (S), Q95.2 (S), Q97.2 (S), Q99.2 (S), Q101.2 (S), Q103.2 (S), Q105.2 (S), Q107.2 (S), Q109.2 (S), Q111.2 (S), Q113.2 (S), Q115.2 (S), Q117.2 (S), Q119.2 (S), Q121.2 (S), Q123.2 (S), Q125.2 (S), Q127.2 (S), Q129.2 (S), Q131.2 (S), Q133.2 (S), Q135.2 (S), Q137.2 (S), Q139.2 (S), Q141.2 (S), Q143.2 (S); also elsewhere on the board

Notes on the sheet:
Status LEDs

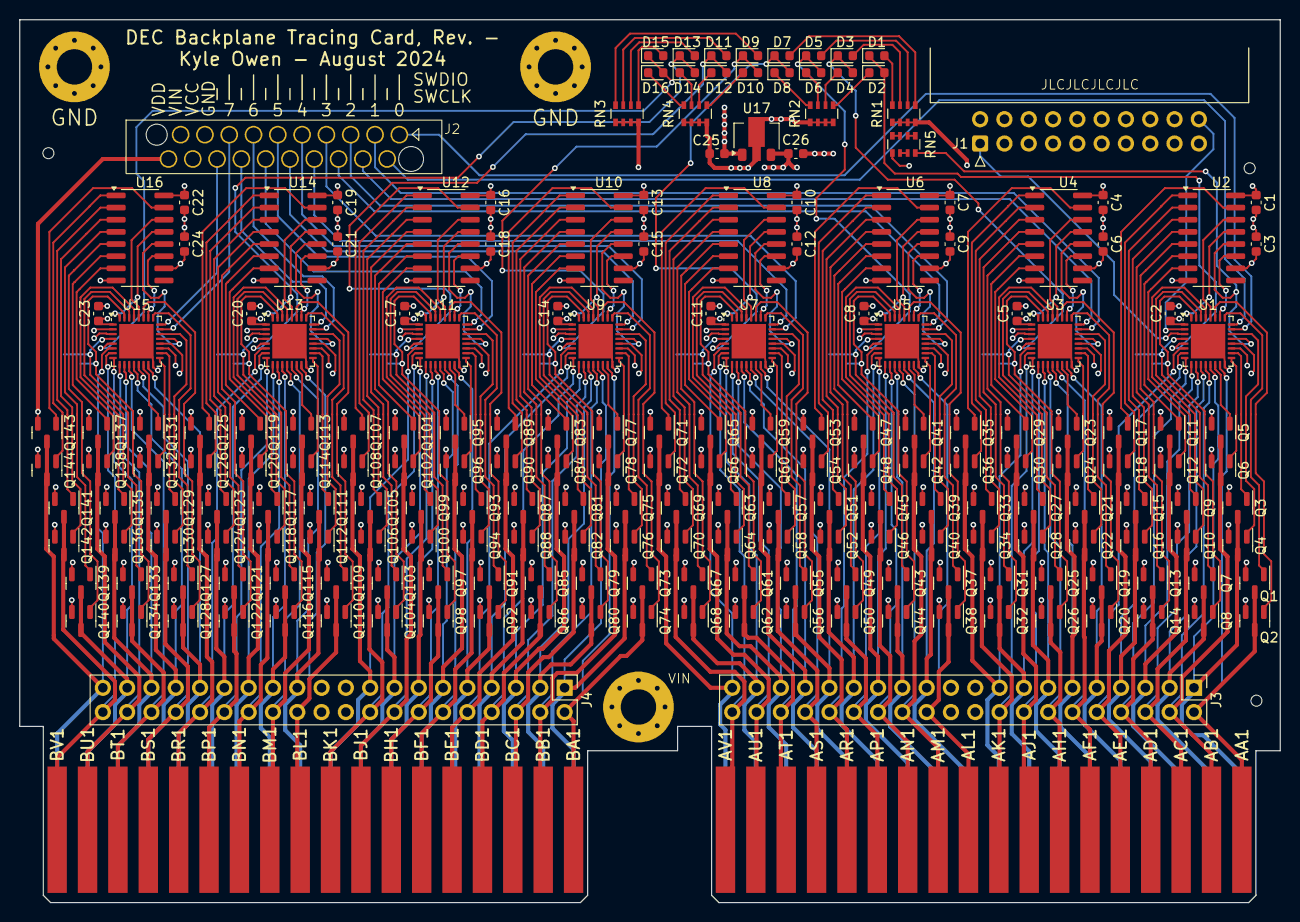
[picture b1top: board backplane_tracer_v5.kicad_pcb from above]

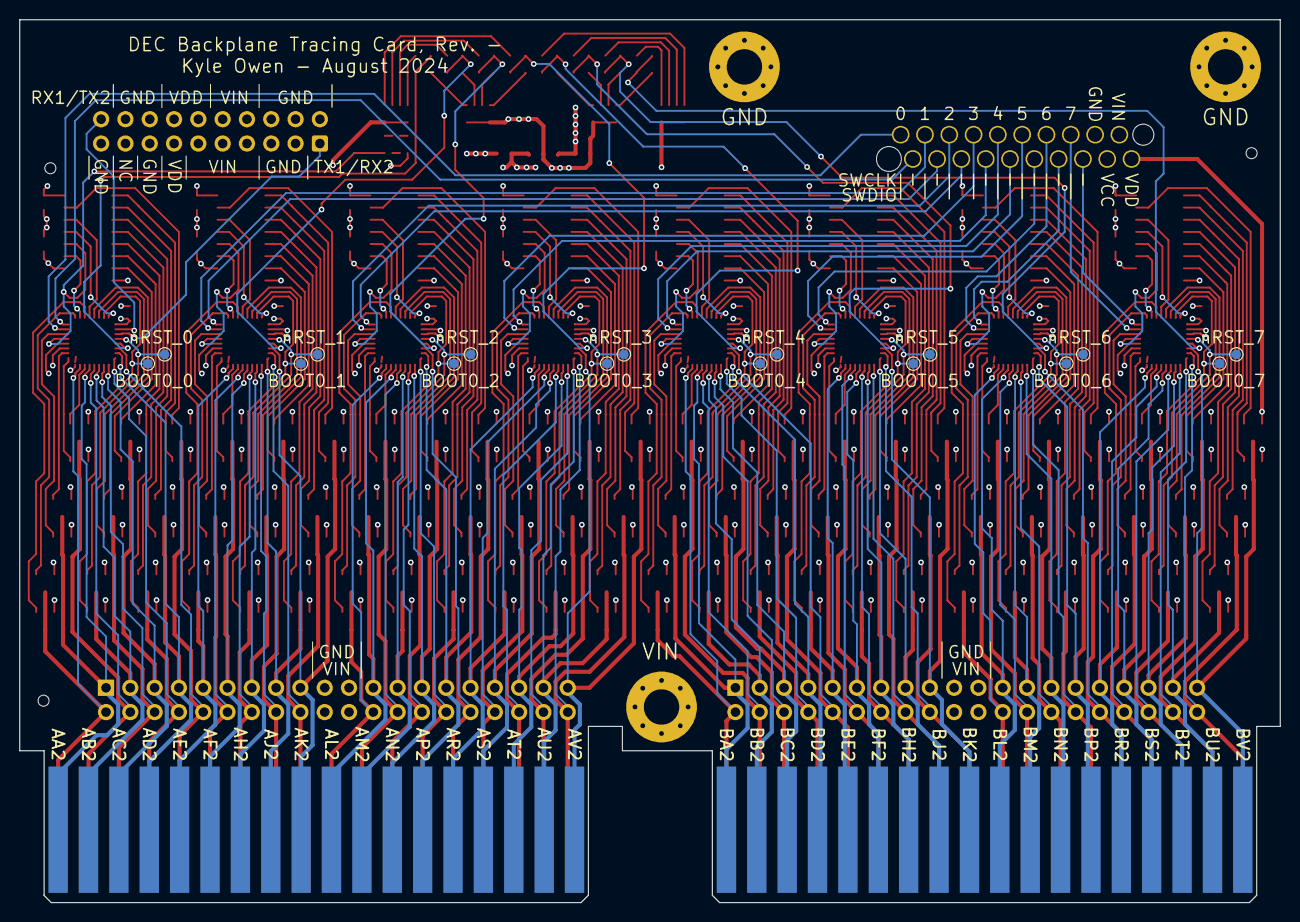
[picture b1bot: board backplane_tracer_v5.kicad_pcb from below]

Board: 4 copper layers, 131.7 x 92.3 mm, 235 parts (16 on the bottom side), 305 nets.
